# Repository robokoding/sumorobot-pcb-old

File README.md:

sumorobot-pcb
=============

The Eagle CAD files for the RoboKoding Sumoboard PCB

bill of materials
=================
ebay
----
* 1 x [switch](http://www.ebay.com/itm/201095465543)
* 1 x [24 pin socket](http://www.ebay.com/itm/221128614182)
* 1 x [USR-WIFI-T module](http://www.ebay.com/itm/251594619856)
* 1 x [3 AA battery holder](http://www.ebay.com/itm/310602601417)
* 1 x [5V step-up converter](http://www.ebay.com/itm/330846857152)
* 1 x [Pro Mini or Pro Micro](http://www.ebay.com/itm/231368307663)
* 1 x [2mm female pin headers](http://www.ebay.com/itm/181108690201)

local electronics store
-----------------------
* 2 x 220Ω resistor
* 2 x 10kΩ resistor
* 1 x 1k8Ω resistor
* 1 x 3k3Ω resistor
* some pin headers

assembly instructions
=====================

documentation
=============
http://www.usriot.com/Product/82.html
http://dangerousprototypes.com/docs/Get_your_PCBs_made

credits ^_^
===========
* https://github.com/bsalinas/huejs
* https://github.com/bjpirt/mirobot-pcb
* https://github.com/sparkfun/SparkFun-Eagle-Libraries

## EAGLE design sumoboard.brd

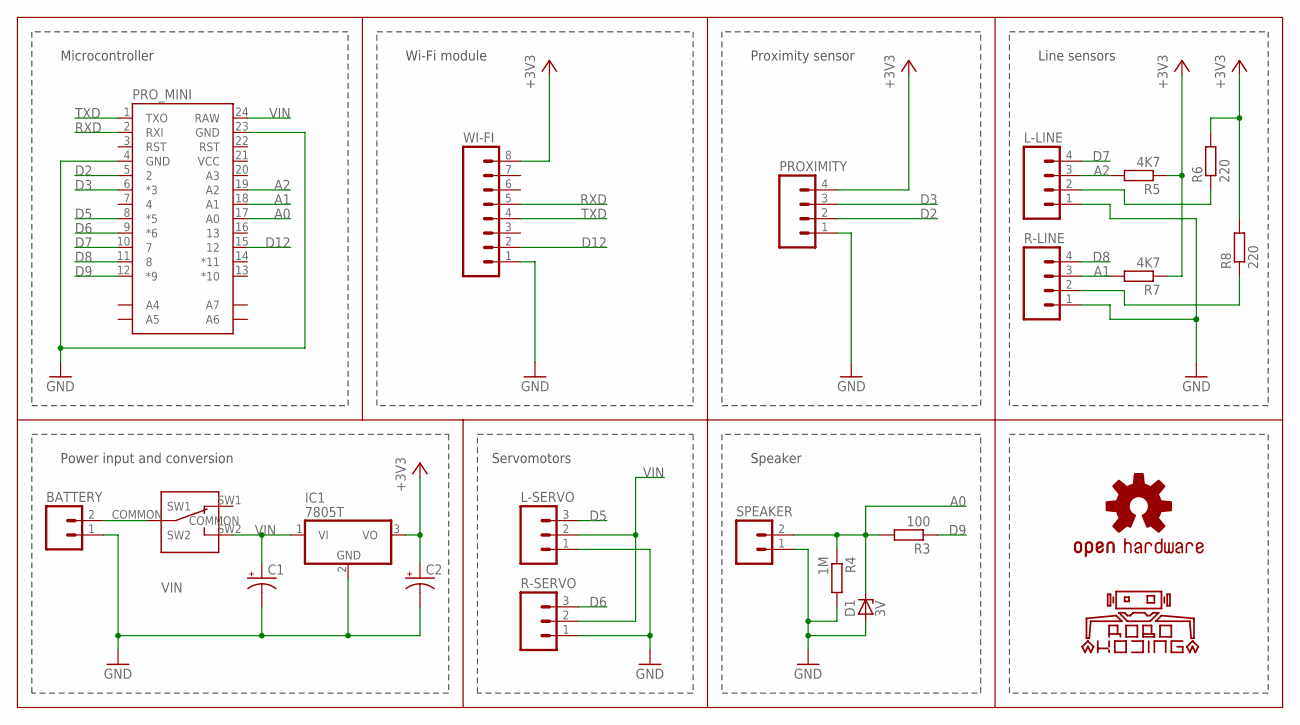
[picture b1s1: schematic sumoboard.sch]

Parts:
BATTERY: M02LOCK_LONGPADS; 1X02_LOCK_LONGPADS
C1, C2: CPOL-USE5-10.5; E5-10,5
D1: 3V; DO35Z10
IC1: 7805T; TO220H
L-LINE: M04LOCK_LONGPADS; 1X04_LOCK_LONGPADS
L-SERVO: M03LOCK_LONGPADS; 1X03_LOCK_LONGPADS
LOGO1: OSHW-LOGOM; OSHW-LOGO-M
LOGO2: ROBOKODING-LOGOM; ROBOKODING-LOGO-M
POWER: SPDT_SLIDE_SWITCH
PROXIMITY: M04LOCK_LONGPADS; 1X04_LOCK_LONGPADS
PRO_MINI: ARDUINO_PRO_MINI
R3: 100; 0204/5
R4: 1M; 0204/5
R5, R7: 4K7; 0204/5
R6, R8: 220; 0204/5
R-LINE: M04LOCK_LONGPADS; 1X04_LOCK_LONGPADS
R-SERVO: M03LOCK_LONGPADS; 1X03_LOCK_LONGPADS
SPEAKER: M02LOCK_LONGPADS; 1X02_LOCK_LONGPADS
WI-FI: M08LOCK_LONGPADS; 1X08_LOCK_LONGPADS

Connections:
+3V3: C2.+, IC1.3 (VO), PROXIMITY.4, R5.1, R6.2, R7.1, R8.2, WI-FI.8
A0: D1.C, PRO_MINI.17 (A0), R3.2, R4.1, SPEAKER.2
A1: PRO_MINI.18 (A1), R7.2, R-LINE.3
A2: L-LINE.3, PRO_MINI.19 (A2), R5.2
BAT_IN: BATTERY.2, POWER.COMMON
D2: PROXIMITY.2, PRO_MINI.5 (2)
D3: PROXIMITY.3, PRO_MINI.6 (*3)
D5: L-SERVO.3, PRO_MINI.8 (*5)
D6: PRO_MINI.9 (*6), R-SERVO.3
D7: L-LINE.4, PRO_MINI.10 (7)
D8: PRO_MINI.11 (8), R-LINE.4
D9: PRO_MINI.12 (*9), R3.1
D12: PRO_MINI.15 (12), WI-FI.2
GND: BATTERY.1, C1.-, C2.-, D1.A, IC1.2 (GND), L-LINE.1, L-SERVO.1, PROXIMITY.1, PRO_MINI.4 (GND), PRO_MINI.23 (GND), R4.2, R-LINE.1, R-SERVO.1, SPEAKER.1, WI-FI.1
unnamed: L-LINE.2, R6.1
unnamed: R8.1, R-LINE.2
RXD: PRO_MINI.2 (RXI), WI-FI.5
TXD: PRO_MINI.1 (TXO), WI-FI.4
VIN: C1.+, IC1.1 (VI), L-SERVO.2, POWER.SW2, PRO_MINI.24 (RAW), R-SERVO.2

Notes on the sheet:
Microcontroller
Wi-Fi module
Power input and conversion
Servomotors
Line sensors
Speaker
Proximity sensor

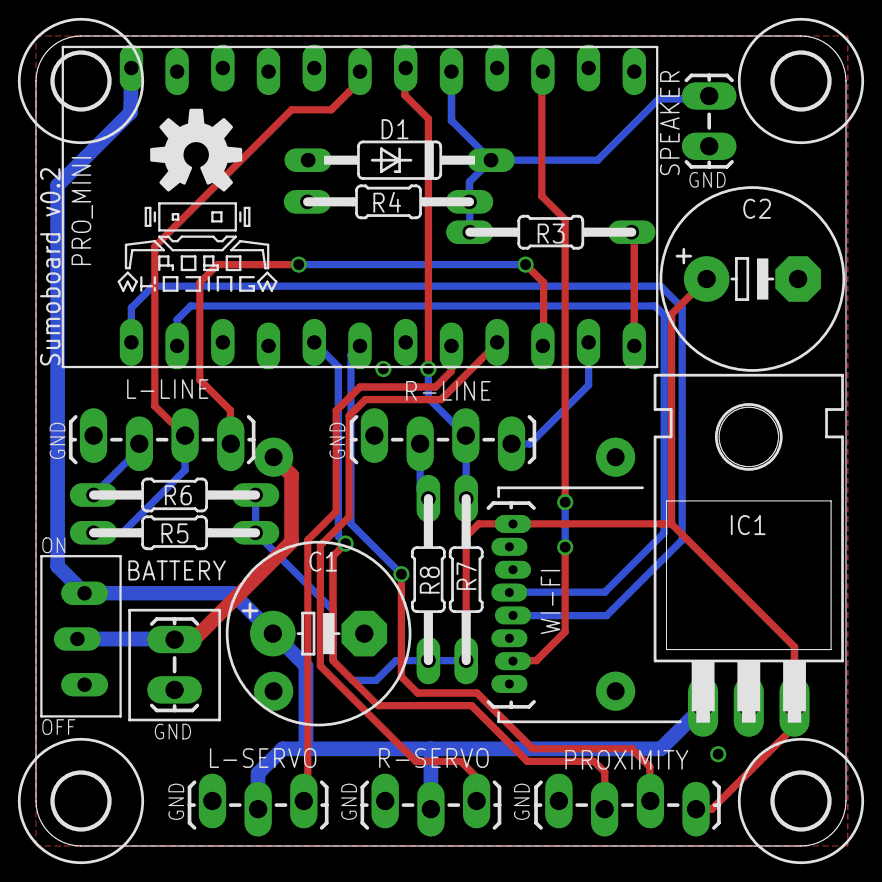
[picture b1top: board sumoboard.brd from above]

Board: 2 copper layers, 45.0 x 45.0 mm, 26 parts (0 on the bottom side), 19 nets.

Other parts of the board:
U$1, U$2, U$3, U$4: 3,0

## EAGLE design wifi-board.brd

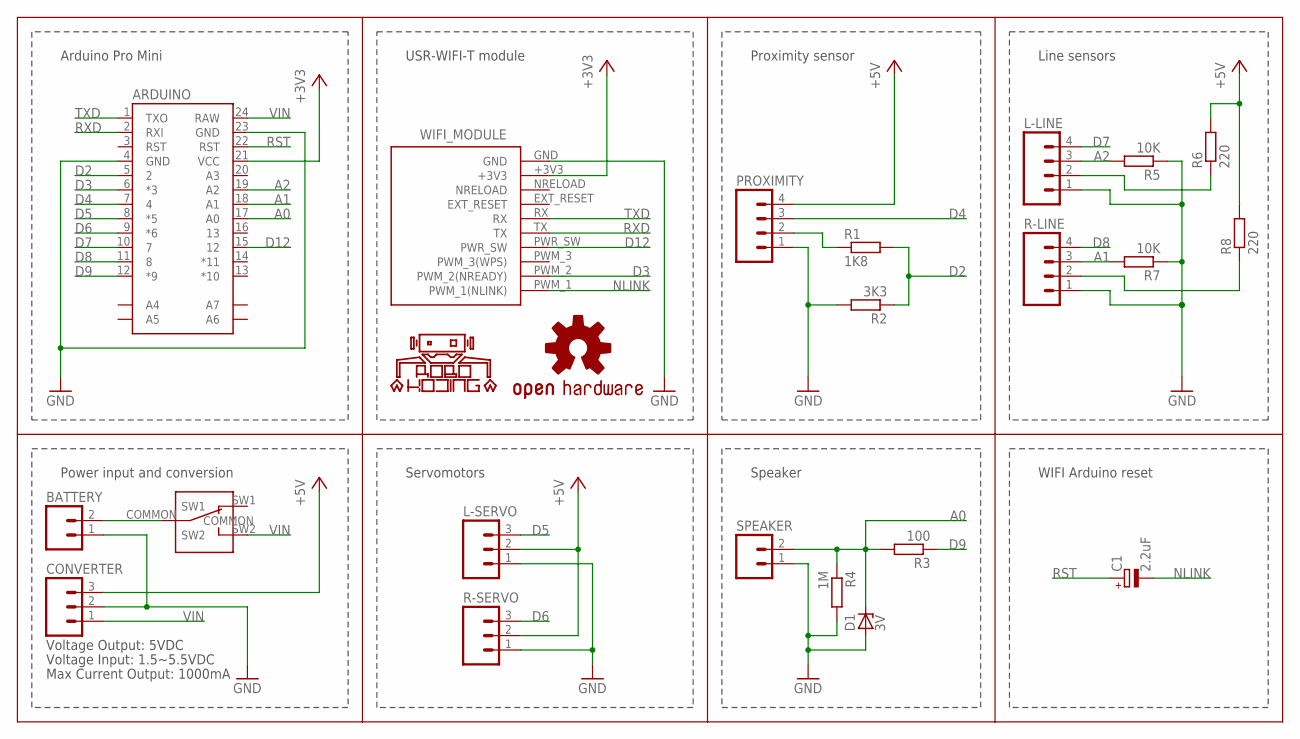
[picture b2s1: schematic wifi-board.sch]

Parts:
ARDUINO: ARDUINO_PRO_MINI
BATTERY: M02JST-PTH-VERT; JST-2-PTH-VERT
C1: 2.2uF; E2-5
CONVERTER: M03LOCK_LONGPADS; 1X03_LOCK_LONGPADS
D1: 3V; DO35Z10
L-LINE: M04LOCK_LONGPADS; 1X04_LOCK_LONGPADS
L-SERVO: M03LOCK_LONGPADS; 1X03_LOCK_LONGPADS
LOGO1: OSHW-LOGOM; OSHW-LOGO-M
LOGO2: ROBOKODING-LOGOM; ROBOKODING-LOGO-M
POWER: SPDT_SLIDE_SWITCH
PROXIMITY: M04LOCK_LONGPADS; 1X04_LOCK_LONGPADS
R1: 1K8; 0204/5
R2: 3K3; 0204/5
R3: 100; 0204/5
R4: 1M; 0204/5
R5, R7: 10K; 0204/5
R6, R8: 220; 0204/5
R-LINE: M04LOCK_LONGPADS; 1X04_LOCK_LONGPADS
R-SERVO: M03LOCK_LONGPADS; 1X03_LOCK_LONGPADS
SPEAKER: M02LOCK_LONGPADS; 1X02_LOCK_LONGPADS
WIFI_MODULE: USR_WIFI-T; WIFI_MODULE-T

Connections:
+3V3: ARDUINO.21 (VCC), WIFI_MODULE.+3V3
+5V: CONVERTER.3, L-SERVO.2, PROXIMITY.4, R6.2, R8.2, R-SERVO.2
A0: ARDUINO.17 (A0), D1.C, R3.2, R4.1, SPEAKER.2
A1: ARDUINO.18 (A1), R7.2, R-LINE.3
A2: ARDUINO.19 (A2), L-LINE.3, R5.2
BAT_IN: BATTERY.2, POWER.COMMON
D2: ARDUINO.5 (2), R1.2, R2.1
D3: ARDUINO.6 (*3), WIFI_MODULE.PWM_2 (PWM_2(NREADY))
D4: ARDUINO.7 (4), PROXIMITY.3
D5: ARDUINO.8 (*5), L-SERVO.3
D6: ARDUINO.9 (*6), R-SERVO.3
D7: ARDUINO.10 (7), L-LINE.4
D8: ARDUINO.11 (8), R-LINE.4
D9: ARDUINO.12 (*9), R3.1
D12: ARDUINO.15 (12), WIFI_MODULE.PWR_SW
GND: ARDUINO.4 (GND), ARDUINO.23 (GND), BATTERY.1, CONVERTER.2, D1.A, L-LINE.1, L-SERVO.1, PROXIMITY.1, R2.2, R4.2, R5.1, R7.1, R-LINE.1, R-SERVO.1, SPEAKER.1, WIFI_MODULE.GND
unnamed: PROXIMITY.2, R1.1
unnamed: L-LINE.2, R6.1
unnamed: R8.1, R-LINE.2
NLINK: C1.-, WIFI_MODULE.PWM_1 (PWM_1(NLINK))
RST: ARDUINO.22 (RST), C1.+
RXD: ARDUINO.2 (RXI), WIFI_MODULE.TX
TXD: ARDUINO.1 (TXO), WIFI_MODULE.RX
VIN: ARDUINO.24 (RAW), CONVERTER.1, POWER.SW2

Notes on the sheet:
Arduino Pro Mini
USR-WIFI-T module
Power input and conversion
Servomotors
Voltage Input: 1.5~5.5VDC
Voltage Output: 5VDC
Max Current Output: 1000mA
Line sensors
Speaker
WIFI Arduino reset
Proximity sensor

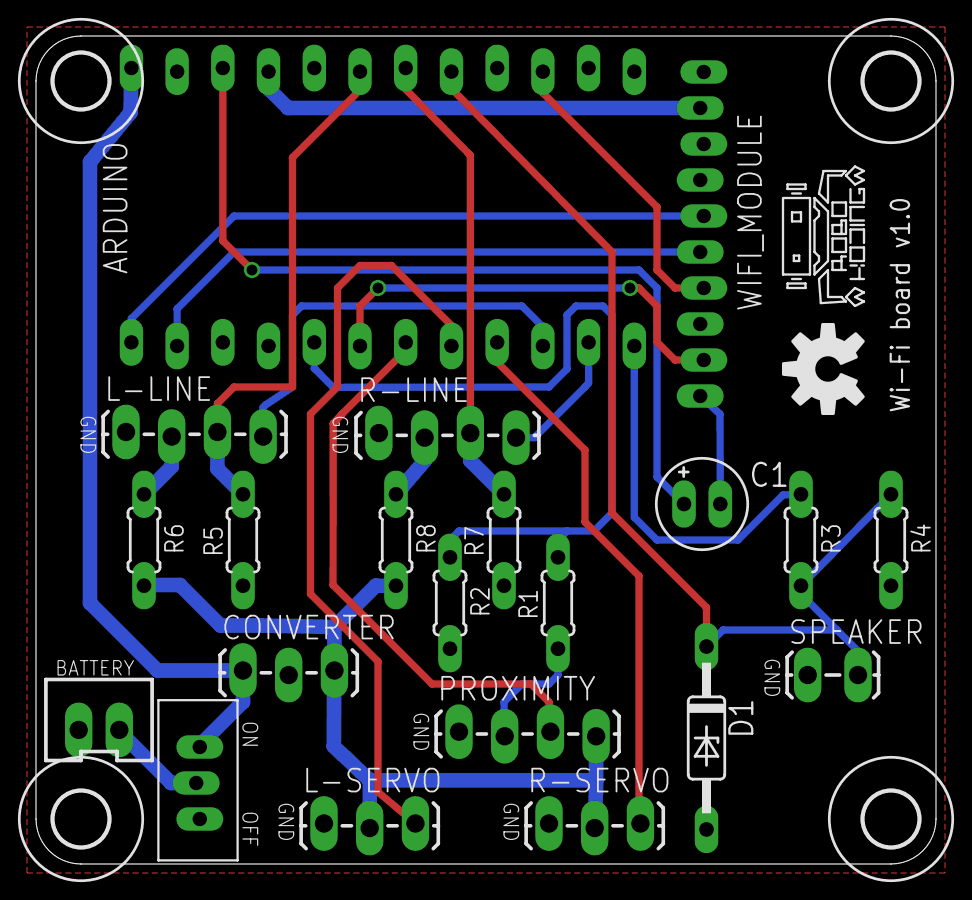
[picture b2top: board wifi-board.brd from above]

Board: 2 copper layers, 50.0 x 46.0 mm, 27 parts (0 on the bottom side), 24 nets.

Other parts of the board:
U$1, U$2, U$3, U$4: 3,0

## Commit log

2014-11-20 added EAGLE schematics and board
2014-11-24 updated battery connector
2015-01-02 updated wifi board
2015-01-11 Update LICENSE
2015-01-20 Rename wifi-board.brd to sumorobot-wifi-pcb.brd
2015-01-20 Rename wifi-board.sch to sumorobot-wifi-pcb.sch
2015-01-29 updated power connector and resistors
2015-01-29 renamed files
2015-02-22 renamed schematics and board
2015-07-30 updated sumoboard
2015-09-08 updated gitignore
2016-05-22 updated component locations

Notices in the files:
parts and their libraries:
SparkFun-Connectors: Licensing: Creative Commons ShareAlike 4.0 International - https://creativecommons.org/licenses/by-sa/4.0
